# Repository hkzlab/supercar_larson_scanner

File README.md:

# "Supercar" Larson Scanner

## Introduction

"Supercar" is the (stupid) italian name for the [Knight Rider](https://en.wikipedia.org/wiki/Knight_Rider_(1982_TV_series)) TV series.
In that series, the iconic car KITT sports a red light going back and forth under the hood. That effect is called "[Larson](https://en.wikipedia.org/wiki/Glen_A._Larson) scanner".

This board implements a "Larson scanner" with regulable speed using a 555 timer and a few 74' CMOS logic ICs (two latches, a full adder, a demux and a 4x 2-in xor gate).
It's powered by a CR2032 coin cell battery.

The circuit is quite simple to understand and a good exercise on SMD hand-soldering.

### Disclaimer

I take NO responsibility for what happens if you decide to build and use this card. But You're encourauged to take what you deem fit from this, and use it in your projects!

## Verilog simulation

You can find a verilog implementation of the circuit under the `supercar_verilog` directory, complete with a testbench.

## Bill of Materials

Remember to use a CMOS variant of the 555 timer compatible with a low supply voltage, like [this](https://www.mouser.it/ProductDetail/926-LMC555CMX-NOPB).

**TODO**

## Required Fixes

### Rev. 1

* Pin 4 of the RN1 resistor network is unconnected and should be connected to +3.3V. Pin 16 of U1 is a good spot.

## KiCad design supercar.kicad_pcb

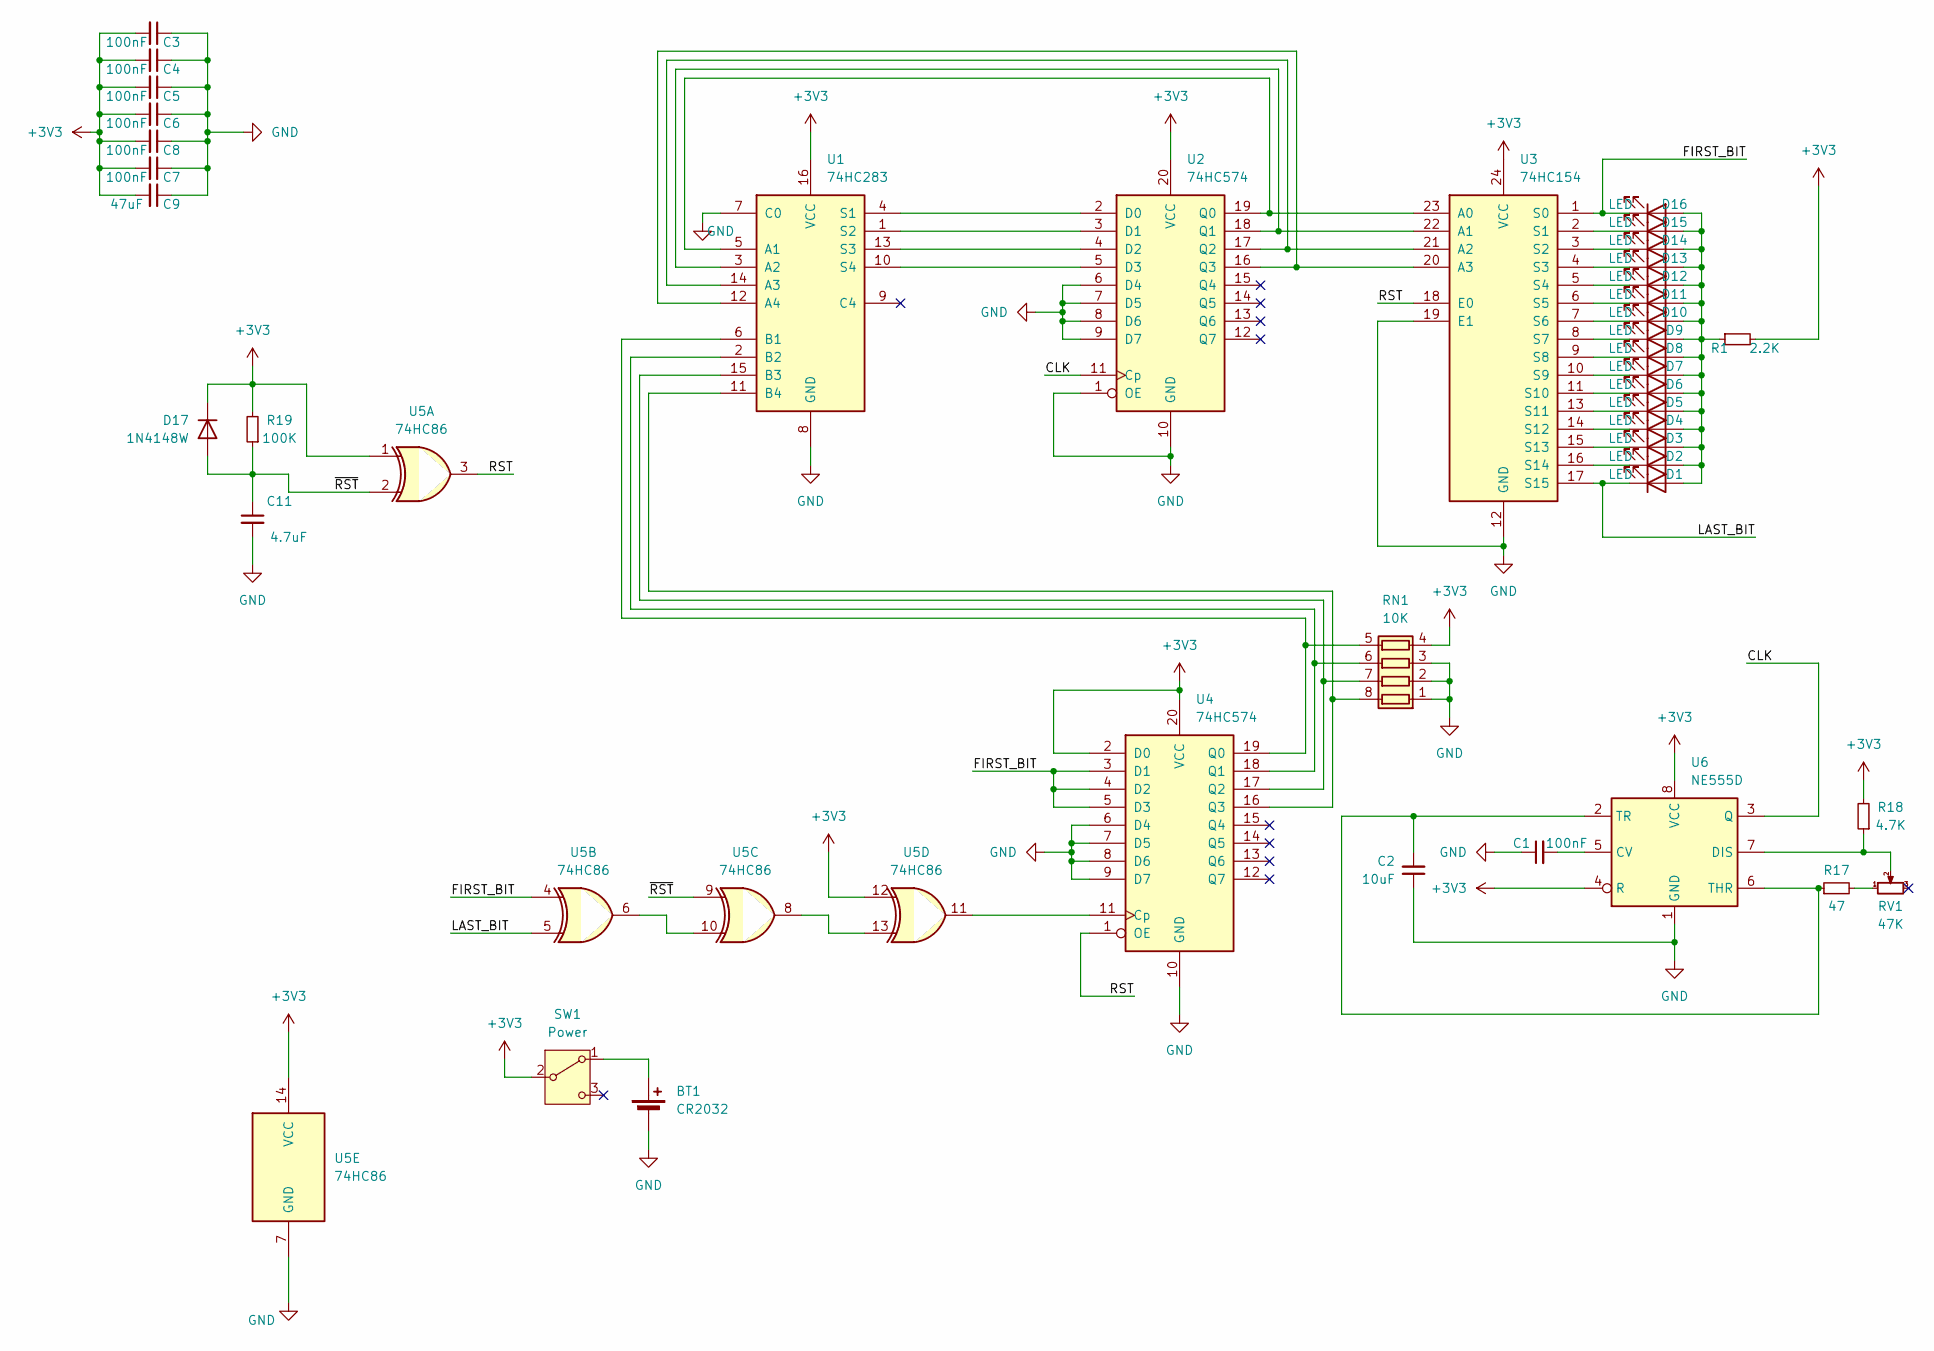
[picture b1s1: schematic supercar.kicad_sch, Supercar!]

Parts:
BT1: CR2032; BatteryHolder_Keystone_1060_1x2032
C1, C3, C4, C5, C6, C7, C8: 100nF; C_1206_3216Metric_Pad1.33x1.80mm_HandSolder
C2: 10uF; C_1206_3216Metric_Pad1.33x1.80mm_HandSolder
C9: 47uF; C_1206_3216Metric_Pad1.33x1.80mm_HandSolder
C11: 4.7uF; C_1206_3216Metric_Pad1.33x1.80mm_HandSolder
D1, D2, D3, D4, D5, D6, D7, D8, D9, D10, D11, D12, D13, D14, D15, D16: LED; LED_1206_3216Metric_Pad1.42x1.75mm_HandSolder
D17: 1N4148W; D_SOD-123
R1: 2.2K; R_1206_3216Metric_Pad1.30x1.75mm_HandSolder
R17: 47; R_1206_3216Metric_Pad1.30x1.75mm_HandSolder
R18: 4.7K; R_1206_3216Metric_Pad1.30x1.75mm_HandSolder
R19: 100K; R_1206_3216Metric_Pad1.30x1.75mm_HandSolder
RN1: 10K; R_Array_Convex_4x0612
RV1: 47K; Potentiometer_Bourns_3314G_Vertical
SW1: Power; SW_Slide_1P2T_CK_OS102011MS2Q
U1: 74HC283; SOIC-16_3.9x9.9mm_P1.27mm
U2, U4: 74HC574; SOIC-20W_7.5x12.8mm_P1.27mm
U3: 74HC154; SOIC-24W_7.5x15.4mm_P1.27mm
U5: 74HC86; SOIC-14_3.9x8.7mm_P1.27mm
U6: NE555D; SOIC-8_3.9x4.9mm_P1.27mm

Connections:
+3V3: C3.2, C4.2, C5.2, C6.2, C7.2, C8.2, C9.2, D17.1 (K), R1.2, R18.2, R19.2, RN1.4 (R4.1), SW1.2 (B), U1.16 (VCC), U2.20 (VCC), U3.24 (VCC), U4.2 (D0), U4.20 (VCC), U5.1, U5.12, U5.14 (VCC), U6.4 (R), U6.8 (VCC)
/CLK: U2.11 (Cp), U6.3 (Q)
/FIRST_BIT: D16.1 (K), U3.1 (S0), U4.3 (D1), U4.4 (D2), U4.5 (D3), U5.4
/LAST_BIT: D1.1 (K), U3.17 (S15), U5.5
/RST: U3.18 (E0), U4.1 (OE), U5.3
/~RST: C11.1, D17.2 (A), R19.1, U5.2, U5.9
GND: BT1.2 (-), C1.1, C2.1, C3.1, C4.1, C5.1, C6.1, C7.1, C8.1, C9.1, C11.2, RN1.1 (R1.1), RN1.2 (R2.1), RN1.3 (R3.1), U1.7 (C0), U1.8 (GND), U2.1 (OE), U2.6 (D4), U2.7 (D5), U2.8 (D6), U2.9 (D7), U2.10 (GND), U3.12 (GND), U3.19 (E1), U4.6 (D4), U4.7 (D5), U4.8 (D6), U4.9 (D7), U4.10 (GND), U5.7 (GND), U6.1 (GND)
unnamed: BT1.1 (+), SW1.1 (A)
unnamed: D1.2 (A), D2.2 (A), D3.2 (A), D4.2 (A), D5.2 (A), D6.2 (A), D7.2 (A), D8.2 (A), D9.2 (A), D10.2 (A), D11.2 (A), D12.2 (A), D13.2 (A), D14.2 (A), D15.2 (A), D16.2 (A), R1.1
unnamed: D2.1 (K), U3.16 (S14)
unnamed: D3.1 (K), U3.15 (S13)
unnamed: D4.1 (K), U3.14 (S12)
unnamed: D5.1 (K), U3.13 (S11)
unnamed: D6.1 (K), U3.11 (S10)
unnamed: D7.1 (K), U3.10 (S9)
unnamed: D8.1 (K), U3.9 (S8)
unnamed: D9.1 (K), U3.8 (S7)
unnamed: D10.1 (K), U3.7 (S6)
unnamed: D11.1 (K), U3.6 (S5)
unnamed: D12.1 (K), U3.5 (S4)
unnamed: D13.1 (K), U3.4 (S3)
unnamed: D14.1 (K), U3.3 (S2)
unnamed: D15.1 (K), U3.2 (S1)
unnamed: R17.2, RV1.1
unnamed: RN1.8 (R1.2), U1.11 (B4), U4.16 (Q3)
unnamed: RN1.7 (R2.2), U1.15 (B3), U4.17 (Q2)
unnamed: RN1.6 (R3.2), U1.2 (B2), U4.18 (Q1)
unnamed: RN1.5 (R4.2), U1.6 (B1), U4.19 (Q0)
unnamed: U1.5 (A1), U2.19 (Q0), U3.23 (A0)
unnamed: U1.3 (A2), U2.18 (Q1), U3.22 (A1)
unnamed: U1.14 (A3), U2.17 (Q2), U3.21 (A2)
unnamed: U1.12 (A4), U2.16 (Q3), U3.20 (A3)
unnamed: U1.4 (S1), U2.2 (D0)
unnamed: U1.1 (S2), U2.3 (D1)
unnamed: U1.13 (S3), U2.4 (D2)
unnamed: U1.10 (S4), U2.5 (D3)
unnamed: U4.11 (Cp), U5.11
unnamed: U5.6, U5.10
unnamed: U5.8, U5.13
unnamed: C1.2, U6.5 (CV)
unnamed: R18.1, RV1.2, U6.7 (DIS)
unnamed: C2.2, R17.1, U6.2 (TR), U6.6 (THR)

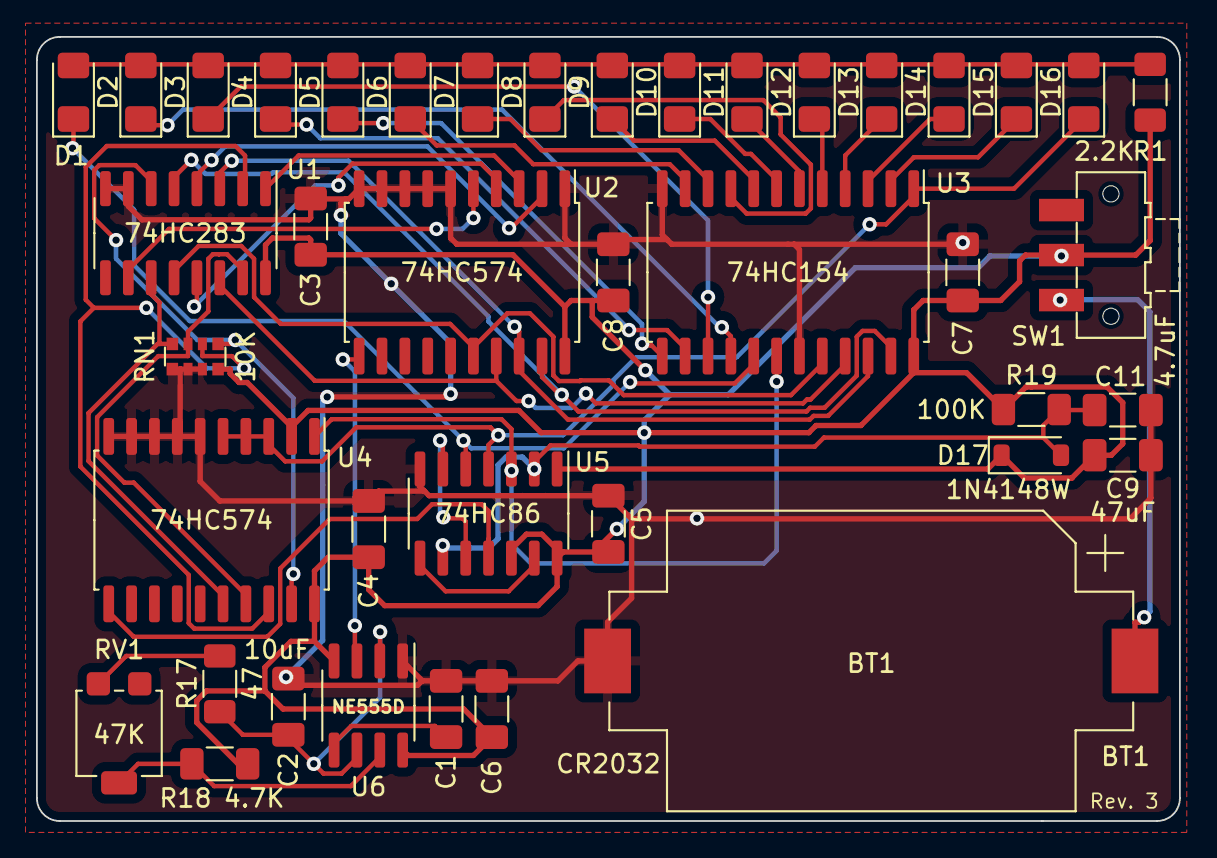
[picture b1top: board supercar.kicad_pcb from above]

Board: 2 copper layers, 63.5 x 43.6 mm, 41 parts (0 on the bottom side), 42 nets.

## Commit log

2024-01-07 Assigned footprints
2024-01-07 add pcb
2024-01-08 Carry bit must be set to 0
2024-01-24 Fix led orientation and connection
2024-01-25 Update the PCB to include a reset circuit
2024-01-25 Reorganize silkscreen a bit
2024-01-25 Use replication operator
2024-01-26 Update schematic and PCB
2024-01-26 Slight change to PCB
2024-01-29 Reduce IC count and reroute the board
2024-02-04 Update schematics
2024-02-04 Use a single resistor, reduce the size of the PCB
2024-02-15 Fix cap position in rev3
2024-02-16 Reroute rev_3
2024-02-16 Update the schematic
2024-02-17 add 47uf cap as buffer to battery
2024-02-17 Resistor led now 2.2K
2024-02-22 Change reset circuit to not turn on leds
2024-02-22 Small change in component value
2024-02-22 Feed the reset circuit on the delay line of the adder clock
2024-02-22 Further changes to the board, changed the switch
2024-02-27 Fix schematics
2024-03-20 Updated readme. again.
2024-03-20 Add note about 555 type
